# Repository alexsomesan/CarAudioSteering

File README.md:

# Car Audio Steering
An microcontroller based adapter for matching steering wheel controls to random car stereo units.

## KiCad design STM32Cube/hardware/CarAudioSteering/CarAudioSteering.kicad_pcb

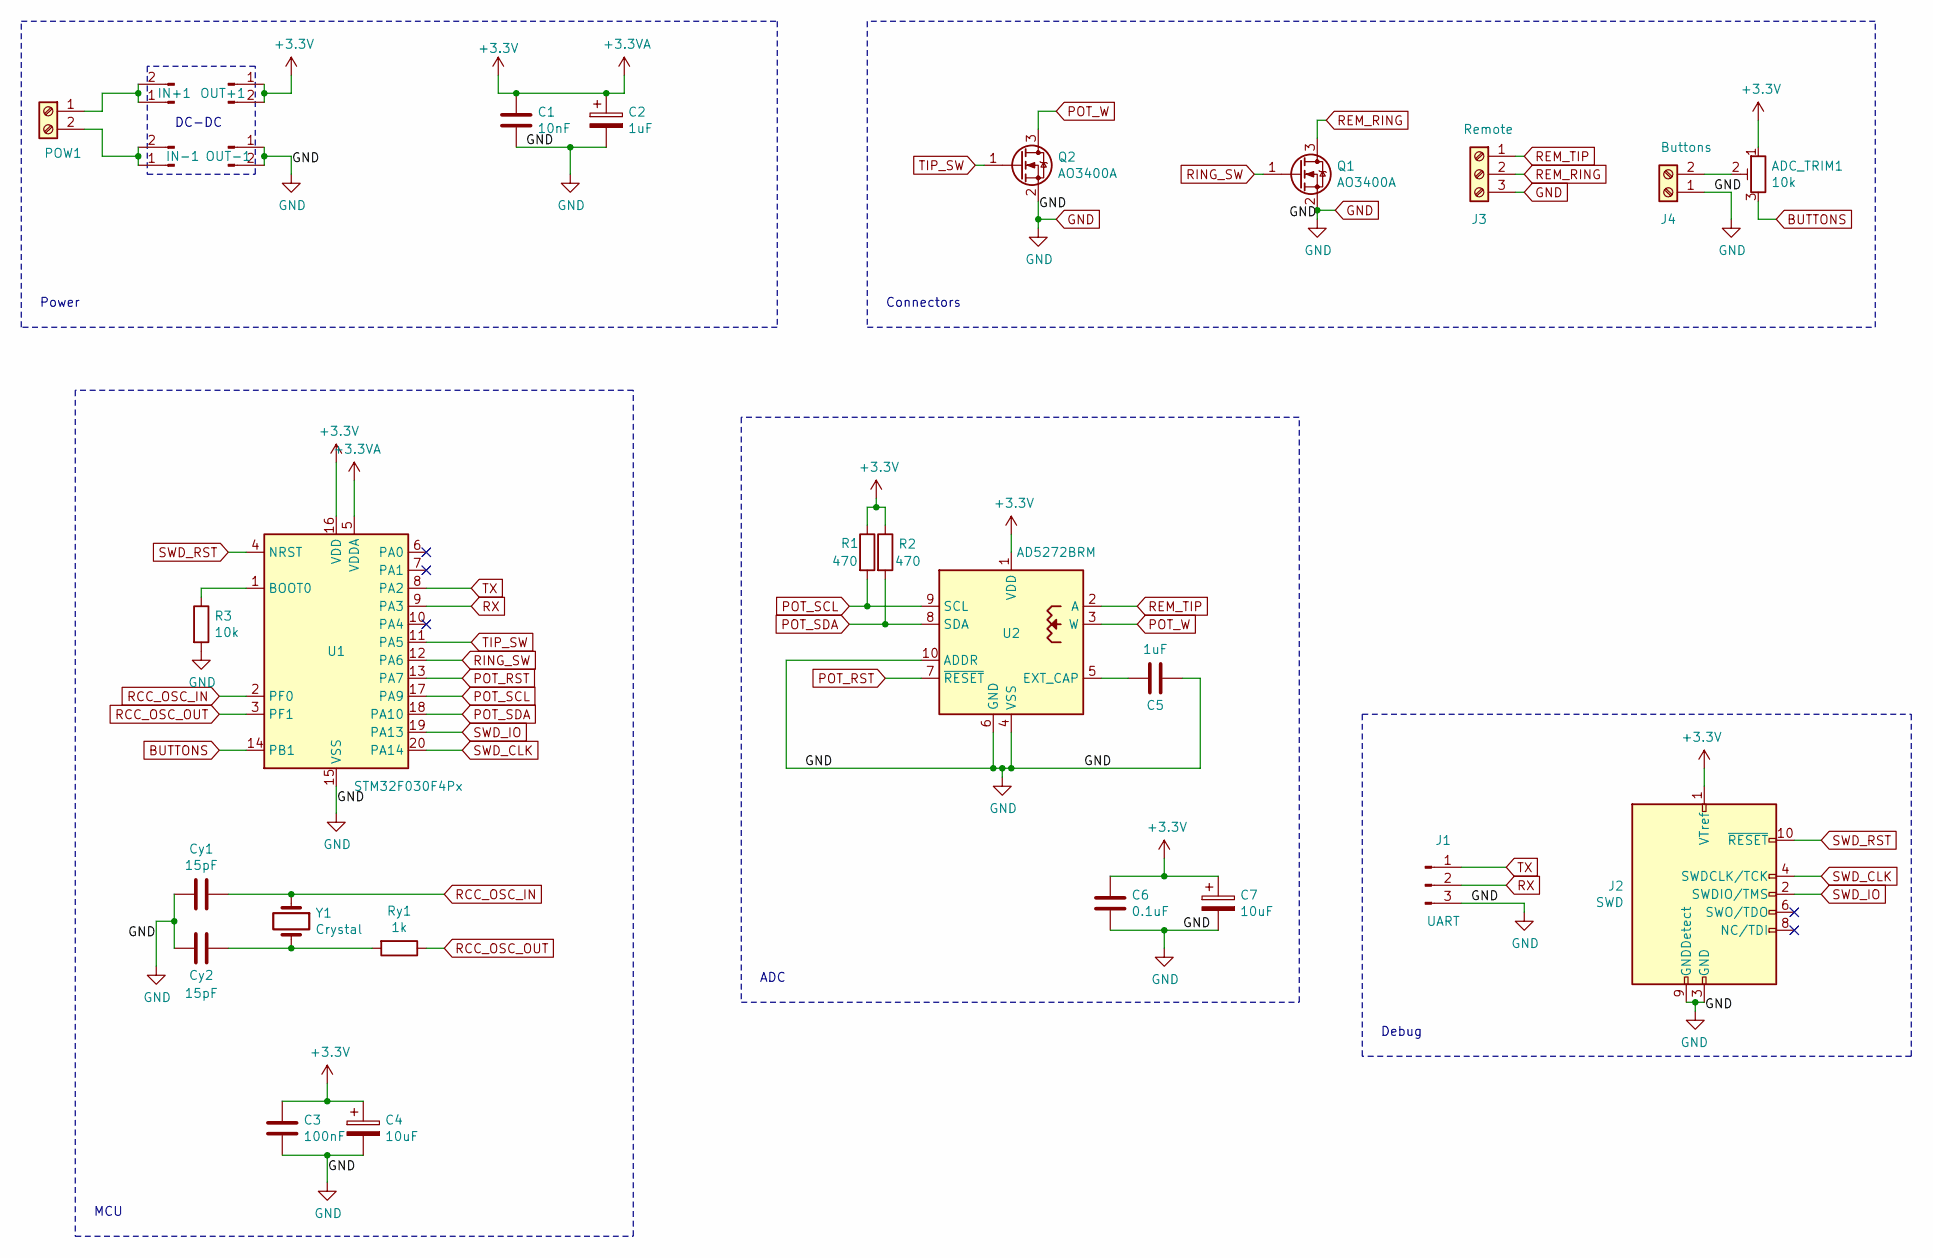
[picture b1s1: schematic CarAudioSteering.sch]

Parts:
ADC_TRIM1: 10k; PinHeader_1x03_P2.54mm_Vertical
C1: 10nF; C_0805_2012Metric
C2, C5: 1uF; C_0805_2012Metric
C3: 100nF; C_0805_2012Metric
C4, C7: 10uF; C_0805_2012Metric
C6: 0.1uF; C_0603_1608Metric
Cy1, Cy2: 15pF; C_0603_1608Metric
IN+1: Conn_01x02_Male; PinHeader_1x02_P2.54mm_Vertical
IN-1: Conn_01x02_Male; PinHeader_1x02_P2.54mm_Vertical
J1: UART; PinHeader_1x03_P2.54mm_Vertical
J2: SWD; PinHeader_2x05_P1.27mm_Vertical_SMD
J3: Remote; TerminalBlock_Phoenix_MPT-0,5-3-2.54_1x03_P2.54mm_Horizontal
J4: Buttons; TerminalBlock_Phoenix_MPT-0,5-2-2.54_1x02_P2.54mm_Horizontal
OUT+1: Conn_01x02_Male; PinHeader_1x02_P2.54mm_Vertical
OUT-1: Conn_01x02_Male; PinHeader_1x02_P2.54mm_Vertical
POW1: Screw_Terminal_01x02; TerminalBlock_Phoenix_MPT-0,5-2-2.54_1x02_P2.54mm_Horizontal
Q1, Q2: AO3400A; SOT-23
R1, R2: 470; R_0603_1608Metric
R3: 10k; R_0603_1608Metric
Ry1: 1k; R_0603_1608Metric
U1: STM32F030F4Px; TSSOP-20_4.4x6.5mm_P0.65mm
U2: AD5272BRM; MSOP-10_3x3mm_P0.5mm
Y1: Crystal; Crystal_SMD_5032-2Pin_5.0x3.2mm

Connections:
+3.3VA: ADC_TRIM1.1, C1.1, C2.1, C3.1, C4.1, C6.1, C7.1, J2.1 (VTref), OUT+1.1, OUT+1.2, R1.1, R2.1, U1.5 (VDDA), U1.16 (VDD), U2.1 (VDD)
BUTTONS: ADC_TRIM1.3, U1.14 (PB1)
GND: C1.2, C2.2, C3.2, C4.2, C5.1, C6.2, C7.2, Cy1.2, Cy2.1, J1.3, J2.3 (GND), J2.5 (GND), J2.9 (GNDDetect), J3.3, J4.1, OUT-1.1, OUT-1.2, Q1.2 (S), Q2.2 (S), R3.2, U1.15 (VSS), U2.4 (VSS), U2.6 (GND), U2.10 (ADDR)
unnamed: ADC_TRIM1.2, J4.2
unnamed: C5.2, U2.5 (EXT_CAP)
unnamed: Cy2.2, Ry1.2, Y1.2
unnamed: IN+1.1, IN+1.2, POW1.1
unnamed: IN-1.1, IN-1.2, POW1.2
unnamed: R3.1, U1.1 (BOOT0)
POT_RST: U1.13 (PA7), U2.7 (~RESET)
POT_SCL: R1.2, U1.17 (PA9), U2.9 (SCL)
POT_SDA: R2.2, U1.18 (PA10), U2.8 (SDA)
POT_W: Q2.3 (D), U2.3 (W)
RCC_OSC_IN: Cy1.1, U1.2 (PF0), Y1.1
RCC_OSC_OUT: Ry1.1, U1.3 (PF1)
REM_RING: J3.2, Q1.3 (D)
REM_TIP: J3.1, U2.2 (A)
RING_SW: Q1.1 (G), U1.12 (PA6)
RX: J1.2, U1.9 (PA3)
SWD_CLK: J2.4 (SWDCLK/TCK), U1.20 (PA14)
SWD_IO: J2.2 (SWDIO/TMS), U1.19 (PA13)
SWD_RST: J2.10 (~RESET~), U1.4 (NRST)
TIP_SW: Q2.1 (G), U1.11 (PA5)
TX: J1.1, U1.8 (PA2)

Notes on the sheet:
DC-DC
Power
MCU
ADC
Debug
Connectors

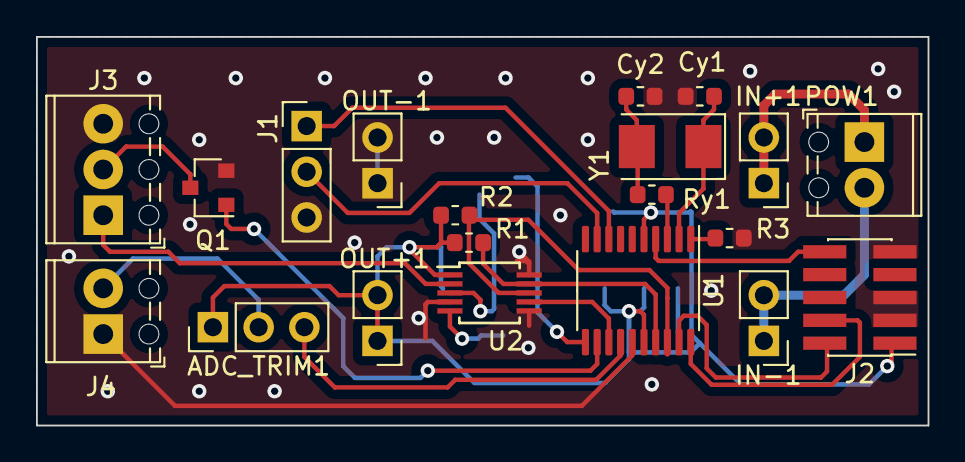
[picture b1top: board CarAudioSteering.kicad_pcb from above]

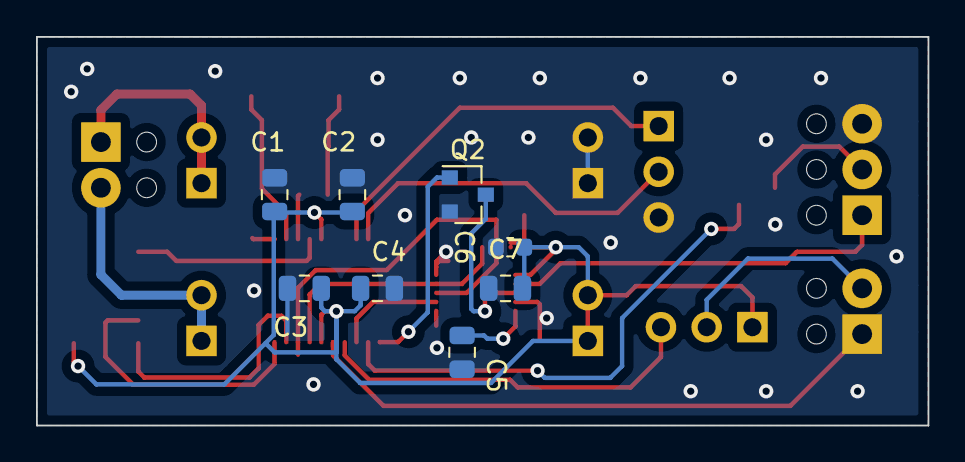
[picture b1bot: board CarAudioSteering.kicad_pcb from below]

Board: 2 copper layers, 49.5 x 21.6 mm, 28 parts (8 on the bottom side), 24 nets.

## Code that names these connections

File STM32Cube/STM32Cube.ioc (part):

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Mcu.Name=STM32F030F4Px
Mcu.Package=TSSOP20
Mcu.UserName=STM32F030F4Px
PA10.GPIOParameters=GPIO_Label
PA10.GPIO_Label=POT_SDA
PA10.Mode=I2C
PA10.Signal=I2C1_SDA
PA13.Mode=Serial_Wire
PA13.Signal=SYS_SWDIO
PA14.Mode=Serial_Wire
PA14.Signal=SYS_SWCLK
PA2.Mode=Asynchronous
PA2.Signal=USART1_TX
PA3.Mode=Asynchronous
PA3.Signal=USART1_RX
PA5.GPIOParameters=GPIO_Speed,GPIO_PuPd,GPIO_Label
PA5.GPIO_Label=TIP_SW
PA5.GPIO_PuPd=GPIO_PULLDOWN
PA5.GPIO_Speed=GPIO_SPEED_FREQ_MEDIUM
PA5.Signal=GPIO_Output
PA6.GPIOParameters=GPIO_Speed,GPIO_PuPd,GPIO_Label
PA6.GPIO_Label=RING_SW
PA6.GPIO_PuPd=GPIO_PULLDOWN
PA6.GPIO_Speed=GPIO_SPEED_FREQ_MEDIUM
PA6.Signal=GPIO_Output
PA7.GPIOParameters=PinState,GPIO_PuPd,GPIO_Label,GPIO_ModeDefaultOutputPP
PA7.GPIO_Label=POT_RST
PA7.GPIO_ModeDefaultOutputPP=GPIO_MODE_OUTPUT_OD
PA7.GPIO_PuPd=GPIO_PULLUP
PA7.PinState=GPIO_PIN_SET
PA7.Signal=GPIO_Output
PA9.GPIOParameters=GPIO_Label
PA9.GPIO_Label=POT_SCL
PA9.Mode=I2C
PA9.Signal=I2C1_SCL
PB1.GPIOParameters=GPIO_Label
PB1.GPIO_Label=BUTTONS
PB1.Mode=IN9
PB1.Signal=ADC_IN9
PF0-OSC_IN.Mode=HSE-External-Oscillator
PF0-OSC_IN.Signal=RCC_OSC_IN
PF1-OSC_OUT.Mode=HSE-External-Oscillator
PF1-OSC_OUT.Signal=RCC_OSC_OUT
RCC.SYSCLKFreq_VALUE=48000000
RCC.SYSCLKSource=RCC_SYSCLKSOURCE_PLLCLK
board=custom

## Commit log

2019-02-03 WIP Prototype - basic commands
2019-02-03 [WIP] Attempt at basic event system & state machine
2019-02-05 Rename project
2019-02-05 Git ignore VS Code settings folder
2019-02-05 Switch to FastADC for reading inputs. Adapt welcome message prompt.
2019-02-06 Small fixes. Make FastADC optional for now. Add test-platform input values.
2019-02-08 Values tuned in-vehicle
2020-07-22 Move Arduino implementation to own folder
2020-07-28 Initial work on STM32Cube version
2020-08-06 ADC reading via DMA and button state machine working
2020-08-06 Button callback system
2020-08-06 Move digipot init out of main()
2020-08-06 Unused variable
2020-08-08 Update CubeMX project
2020-08-08 * double buffer ADC averaging * configure button output values
2020-08-08 Allocate DMA buffer dynamically
2020-08-11 Simplify state machine & experimental filtering
2020-08-11 explicit source dir in pio.ini
2020-08-11 Some more cleanup
2020-08-11 Initial hardware design (KiCad project)
2020-08-11 Add digitpot output to button handlers
2020-08-13 Actual input values for Mistubishi Lancer VIII
2020-08-14 Add host app
2020-08-14 Implement host app commands + reformatting
2020-08-14 Host app: only send commands when connected
2020-08-19 Minimal ADC forwarding
2020-08-20 Fix switch case statement
2020-08-20 Host app: log 0x02 command
2020-08-20 STM32: use openocd for upload
2020-08-20 Move sources to ./Src
2020-08-21 Git ignore build artefacts
2020-08-21 Remove build artefacts from git
2020-08-21 Cut down on logging in firmware to optimize bin size
2020-08-21 Realtime ADC value display in HostApp
2020-08-21 Display raw ADC val in Host app
2020-08-21 Settle for 115200 baud speed
2020-10-22 Re-implementation with STM32F0 + a first PCB draft (#1)
    STM32Cube version
2020-10-22 Remove unmaintained Arduino version
2020-10-22 Update PCB to add a MOSFET switch on the digipot output
2020-10-30 Some cleanup
2020-10-30 Fix build issue with Qt signals
2020-10-30 Implement connection handshake
2020-10-30 Implement MOS gateway on TIP pin
2020-10-30 Fix build after rebase
2020-11-06 Implement port override
2021-08-30 HostApp: don't close port between connection retries + 0xFAFBFCFD handshake token
2021-08-31 Fix jlink
2021-08-31 Debug as build config + improved handshake
2021-09-02 Consolidate handshake and fix digipot initialization
2021-09-02 Consolidate handshake and add disconnect token
2021-09-02 Some flash storage work
2021-09-02 Trigger saving to flash from UI
2021-09-02 manual pot correction
2021-09-02 Set actuall command values from car
2021-09-03 Fix command output routines
